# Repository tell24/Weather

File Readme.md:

Weather

This is a home project to measure the following parameters without any moving parts:-

	Inside Temperature
	Inside Humidity
	
	Outside Temperature
	Outside Humidity

	Air Pressure

	Rain Fall  Rate  mm/hr
	Total Rain Fall  mm

	Wind Speed mean
	Wind Speed Gust
	Wind Direction

The system will use a variety of micro processors including dSPIC, ESP8266 and Arduino Boards.
Data will be stored on a google sheet.
Display of data will by by GitHub Pages

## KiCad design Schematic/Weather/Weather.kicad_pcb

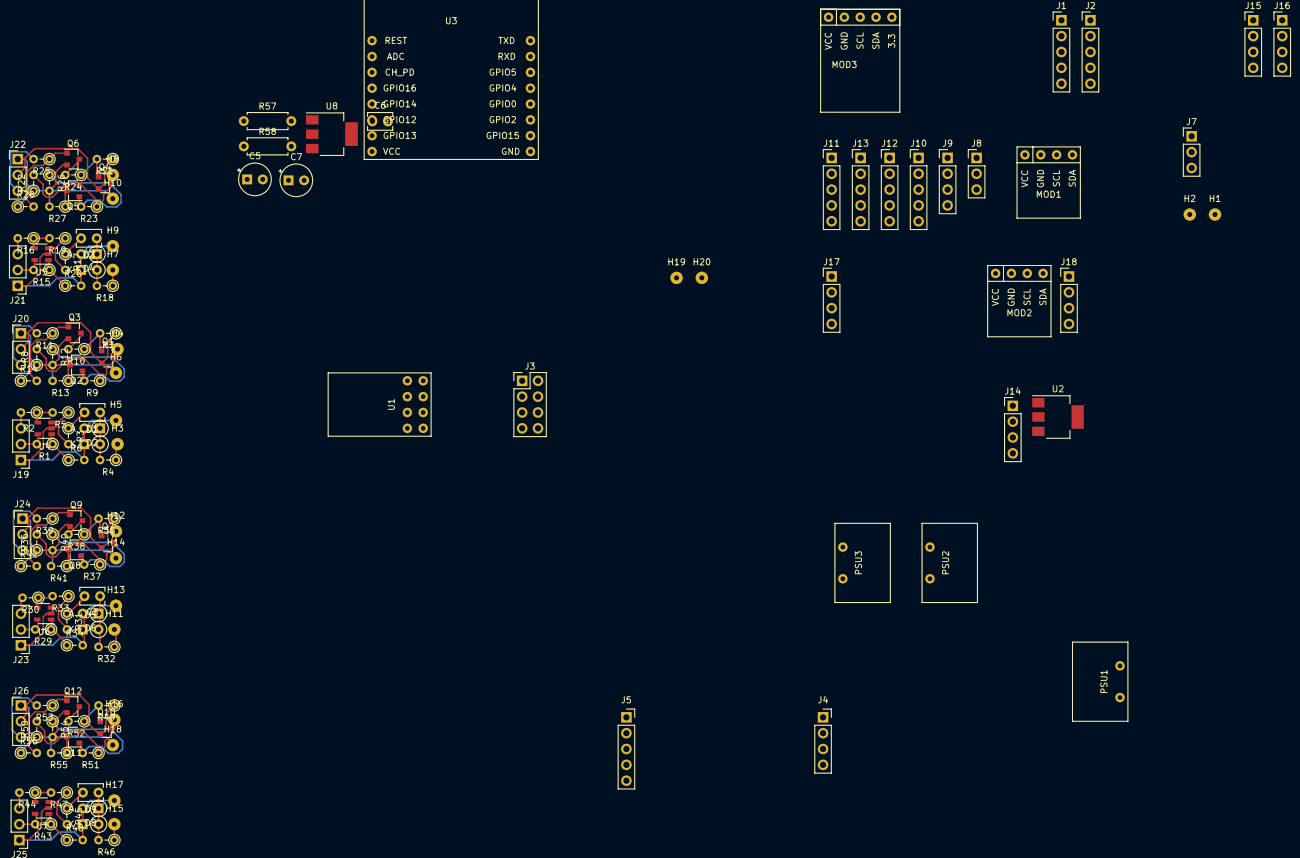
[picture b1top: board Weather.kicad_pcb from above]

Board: 2 copper layers, 144 parts (0 on the bottom side), 77 nets.

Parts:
C1, C2, C3, C4, C6: 0.1uF; C_Disc_D3.8mm_W2.6mm_P2.50mm
C5, C7: 47uF; CP_Radial_Tantal_D5.0mm_P2.50mm
D1, D3, D5, D7: in916; D_DO-35_SOD27_P2.54mm_Vertical_KathodeUp
D2, D4, D6, D8: in916; D_DO-35_SOD27_P2.54mm_Vertical_AnodeUp
H1, H2, H3, H4, H5, H6, H7, H8, H9, H10, H11, H12, H13, H14, H15, H16, H17, H18, H19, H20: MountingHole_Pad; SolderWirePad_1x01_Drill0.8mm
J1: Conn_01x05_Female; PinHeader_1x05_P2.54mm_Vertical
J2: Conn_01x04_Female; PinHeader_1x05_P2.54mm_Vertical
J3: Conn_02x04_Odd_Even; PinHeader_2x04_P2.54mm_Vertical
J4: 4_Way_Wire; PinSocket_1x04_P2.54mm_Vertical
J5: 5_Way_Wire; PinSocket_1x05_P2.54mm_Vertical
J7, J8, J19, J20, J21, J22, J23, J24, J25, J26: 3_Way_Wire; PinHeader_1x03_P2.54mm_Vertical
J9, J14, J15, J16, J17, J18: 4_Way_Wire; PinHeader_1x04_P2.54mm_Vertical
J10, J11, J12, J13: 5_Way_Wire; PinHeader_1x05_P2.54mm_Vertical
MOD1, MOD2: HTU21
MOD3: BMP180
PSU1, PSU2, PSU3: PowerBrick
Q1, Q2, Q4, Q5, Q7, Q8, Q10, Q11: AO3401; SOT-23
Q3, Q6, Q9, Q12: BSS138; SOT-23
R1, R2, R3, R5, R6, R15, R16, R17, R19, R20, R29, R30, R31, R33, R34, R43, R44, R45, R47, R48: 4.7K; R_Axial_DIN0204_L3.6mm_D1.6mm_P2.54mm_Vertical
R4, R18, R32, R46: 3.3k; R_Axial_DIN0204_L3.6mm_D1.6mm_P2.54mm_Vertical
R7, R21, R35, R49: 2.2k; R_Axial_DIN0204_L3.6mm_D1.6mm_P2.54mm_Vertical
R8, R22, R36, R50: 47K; R_Axial_DIN0204_L3.6mm_D1.6mm_P2.54mm_Vertical
R9, R12, R23, R26, R37, R40, R51, R54: 20K; R_Axial_DIN0204_L3.6mm_D1.6mm_P2.54mm_Vertical
R10, R24, R38, R52: 10K; R_Axial_DIN0204_L3.6mm_D1.6mm_P2.54mm_Vertical
R11, R25, R39, R53: 2.2K; R_Axial_DIN0204_L3.6mm_D1.6mm_P2.54mm_Vertical
R13, R27, R41, R55: 680; R_Axial_DIN0204_L3.6mm_D1.6mm_P2.54mm_Vertical
R14, R28, R42, R56: 5.1K; R_Axial_DIN0204_L3.6mm_D1.6mm_P2.54mm_Vertical
R57, R58: 4.7K; R_Axial_DIN0207_L6.3mm_D2.5mm_P7.62mm_Horizontal
U1: ESP-01v090; ESP-01
U2, U8: AMS1117; SOT-223-3_TabPin2
U3: ESP-12; ESP-12_breakout
U4, U5, U6, U7: LM321; SOT-23-5

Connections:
/Anenometer Control Board/J10_P1: D1.1, D2.2, H5.1, H6.1, J19.1, J20.1, Q3.2, R6.2, R8.1, R12.2, R13.2, R14.1, U4.2
/Anenometer Control Board/J10_P2: J19.2, R1.2, U4.5
/Anenometer Control Board/J10_P3: J19.3, R2.2
/Anenometer Control Board/J10_P4: J20.2, Q1.2, R7.1
/Anenometer Control Board/J10_P5: J20.3, R11.2
/Anenometer Control Board/J11_P2: J21.2, R15.2, U5.5
/Anenometer Control Board/J11_P3: J21.3, R16.2
/Anenometer Control Board/J11_P4: J22.2, Q4.2, R21.1
/Anenometer Control Board/J11_P5: J22.3, R25.2
/Anenometer Control Board/J12_P1: D5.1, D6.2, H13.1, H14.1, J23.1, J24.1, Q9.2, R34.2, R36.1, R40.2, R41.2, R42.1, U6.2
/Anenometer Control Board/J12_P2: J23.2, R29.2, U6.5
/Anenometer Control Board/J12_P3: J23.3, R30.2
/Anenometer Control Board/J12_P4: J24.3, R39.2
/Anenometer Control Board/J12_P5: J24.2, Q7.2, R35.1
/Anenometer Control Board/J13_P1: D7.1, D8.2, H17.1, H18.1, J25.1, J26.1, Q12.2, R48.2, R50.1, R54.2, R55.2, R56.1, U7.2
/Anenometer Control Board/J13_P2: J25.2, R43.2, U7.5
/Anenometer Control Board/J13_P3: J25.3, R44.2
/Anenometer Control Board/J13_P4: J26.2, Q10.2, R49.1
/Anenometer Control Board/J13_P5: J26.3, R53.2
/External ESP8266/J14_P1: J14.1, J15.1, J16.1, J17.1, J18.1, MOD2.1, U2.1
/External ESP8266/J14_P2: J14.2, J15.2, J16.2, J17.2, J18.2, MOD2.2, U3.6
/External ESP8266/J14_P3: J14.3, J15.3, J16.3, J17.3, J18.3, MOD2.3, U3.7
/External ESP8266/J14_P4: J14.4, J15.4, J16.4, J17.4, J18.4, MOD2.4, U2.3, U3.9
/Int Motherboard/J0_P2: C5.1, H1.1, H19.1, J1.4, J2.4, J4.4, J5.4, MOD1.4, MOD3.1, PSU1.2, U8.3
/Int Motherboard/J1_P2: J1.2, J2.2, J3.3, J4.2, J5.2, MOD1.2, MOD3.3, R58.2, U1.3
/Int Motherboard/J1_P3: J1.3, J2.3, J3.5, J4.3, J5.3, MOD1.3, MOD3.4, R57.2, U1.5
/Int Motherboard/J3_P6: C6.1, C7.1, J3.7, R57.1, R58.1, U1.7, U8.2
/PSU 2/J7_P1: J7.1, PSU2.2
/PSU 2/J7_P2: J7.2, PSU2.1, PSU3.1
/PSU 2/J7_P3: J7.3, PSU3.2
GND: C5.2, C6.2, C7.2, H2.1, H20.1, J1.1, J2.1, J3.2, J4.1, J5.1, MOD1.1, MOD3.2, PSU1.1, U1.2, U8.1
GNDS: D3.1, D4.2, H9.1, H10.1, J21.1, J22.1, Q6.2, R20.2, R22.1, R26.2, R27.2, R28.1, U5.2
unnamed: C1.1, D1.2, D2.1, R4.2
unnamed: C1.2, R3.1
unnamed: C2.1, D3.2, D4.1, R18.2
unnamed: C2.2, R17.1
unnamed: C3.1, D5.2, D6.1, R32.2
unnamed: C3.2, R31.1
unnamed: C4.1, D7.2, D8.1, R46.2
unnamed: C4.2, R45.1
unnamed: H3.1, H4.1, Q1.3, Q2.2, R4.1, R8.2, R9.1
unnamed: H7.1, H8.1, Q4.3, Q5.2, R18.1, R22.2, R23.1
unnamed: H11.1, H12.1, Q7.3, Q8.2, R32.1, R36.2, R37.1
unnamed: H15.1, H16.1, Q10.3, Q11.2, R46.1, R50.2, R51.1
unnamed: Q1.1, R7.2, R10.1
unnamed: Q2.1, R9.2, R12.1
unnamed: Q2.3, R13.1
unnamed: Q3.1, R11.1, R14.2
unnamed: Q3.3, R10.2
unnamed: Q4.1, R21.2, R24.1
unnamed: Q5.1, R23.2, R26.1
unnamed: Q5.3, R27.1
unnamed: Q6.1, R25.1, R28.2
unnamed: Q6.3, R24.2
unnamed: Q7.1, R35.2, R38.1
unnamed: Q8.1, R37.2, R40.1
unnamed: Q8.3, R41.1
unnamed: Q9.1, R39.1, R42.2
unnamed: Q9.3, R38.2
unnamed: Q10.1, R49.2, R52.1
unnamed: Q11.1, R51.2, R54.1
unnamed: Q11.3, R55.1
unnamed: Q12.1, R53.1, R56.2
unnamed: Q12.3, R52.2
unnamed: R1.1, R6.1, U4.1
unnamed: R2.1, R5.2, U4.4
unnamed: R3.2, R5.1, U4.3
unnamed: R15.1, R20.1, U5.1
unnamed: R16.1, R19.2, U5.4
unnamed: R17.2, R19.1, U5.3
unnamed: R29.1, R34.1, U6.1
unnamed: R30.1, R33.2, U6.4
unnamed: R31.2, R33.1, U6.3
unnamed: R43.1, R48.1, U7.1
unnamed: R44.1, R47.2, U7.4
unnamed: R45.2, R47.1, U7.3
unnamed: U2.2, U3.8

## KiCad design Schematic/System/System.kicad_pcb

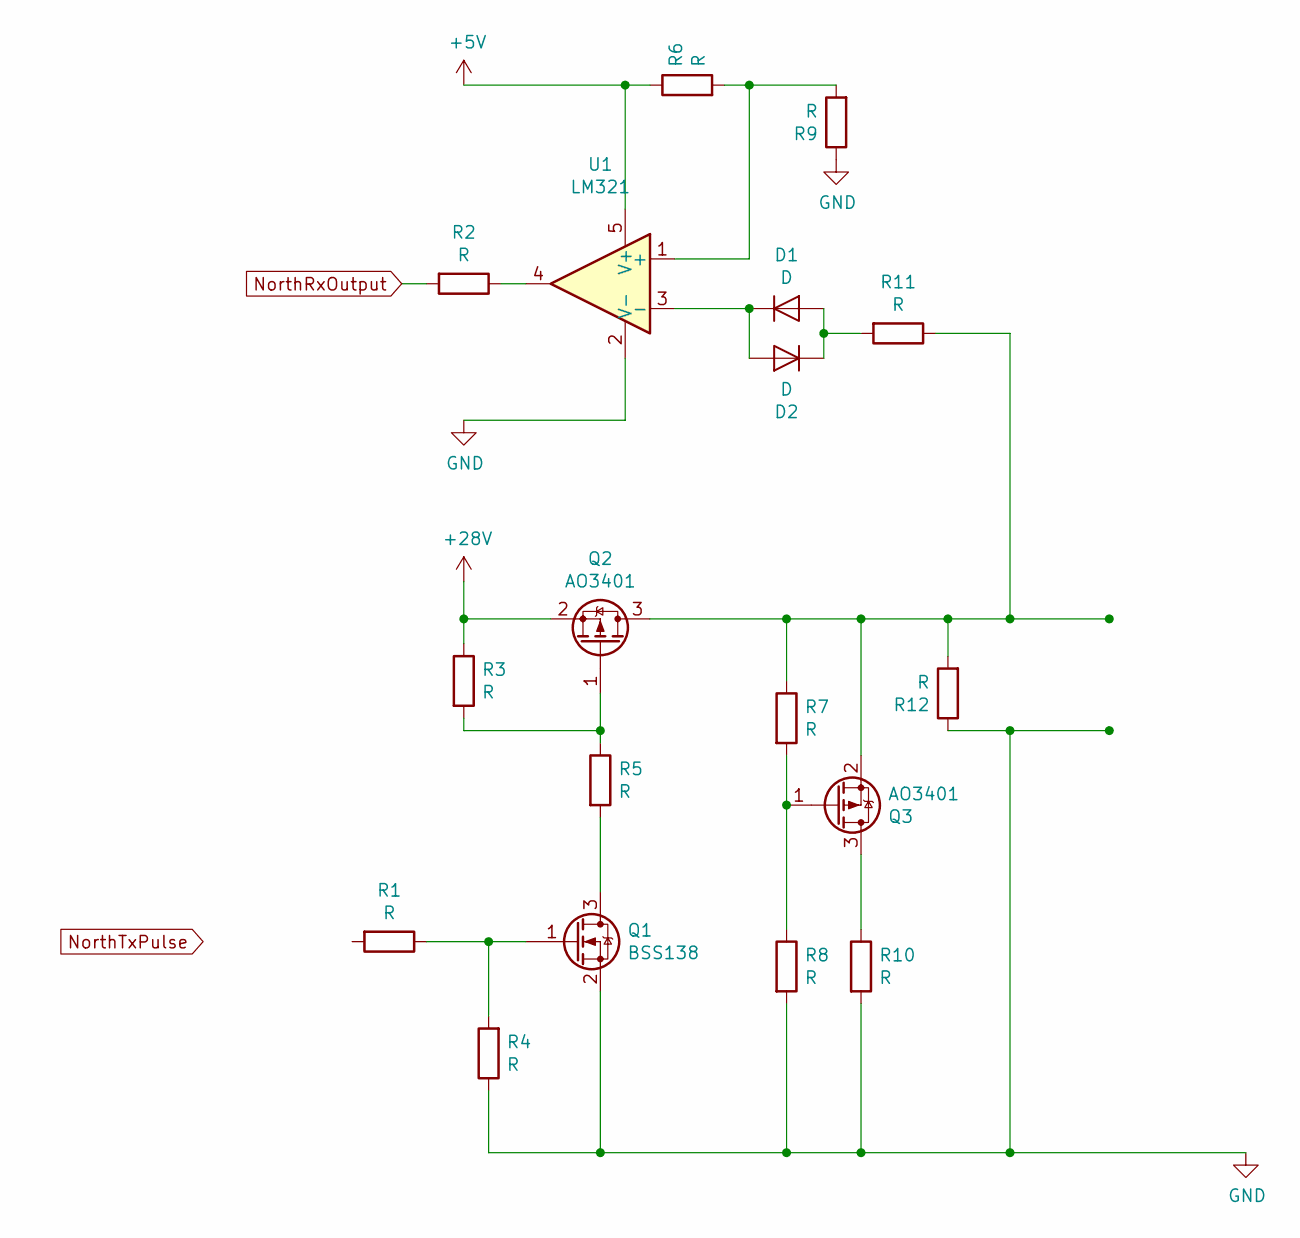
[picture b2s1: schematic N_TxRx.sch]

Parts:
D1, D2: D; D_DO-35_SOD27_P7.62mm_Horizontal
Q1: BSS138; SOT-23
Q2, Q3: AO3401; SOT-23
R1, R2, R3, R4, R5, R6, R7, R8, R9, R10, R11, R12: R; R_Axial_DIN0207_L6.3mm_D2.5mm_P7.62mm_Horizontal
U1: LM321; SOT-23-5

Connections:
+5V: R6.1, U1.5 (V+)
+28V: Q2.2 (S), R3.1
GND: Q1.2 (S), R4.1, R8.2, R9.1, R10.2, R12.1, U1.2 (V-)
unnamed: D1.1 (K), D2.2 (A), U1.3 (-)
unnamed: D1.2 (A), D2.1 (K), R11.2
unnamed: Q1.1 (G), R1.1, R4.2
unnamed: Q1.3 (D), R5.2
unnamed: Q2.1 (G), R3.2, R5.1
unnamed: Q2.3 (D), Q3.2 (S), R7.1, R11.1, R12.2
unnamed: Q3.1 (G), R7.2, R8.1
unnamed: Q3.3 (D), R10.1
unnamed: R2.1, U1.4
unnamed: R6.2, R9.2, U1.1 (+)
NorthRxOutput: R2.2

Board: 2 copper layers, 18 parts (0 on the bottom side), 13 nets, no tracks yet.

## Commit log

2019-02-12 Add readme text
2019-02-12 Elements added all sensors and webPage
2019-02-12 Publish webPage
2019-02-12 index moved
2019-02-13 esp8266 interrupt trigger
2019-02-14 correct high Hum to less than 100%
2019-02-14 Pointers added to gauges
2019-02-14 Temp Hum working
2019-02-15 wind
2019-02-15 pressure dial
2019-02-15 publish
2019-02-15 gust
2019-02-16 Peak
2019-02-16 Dial colour Black
2019-02-16 pre Dial Black
2019-02-16 Max Hum 100%
2019-02-16 Start rain
2019-02-17 rain
2019-02-17 pre ran
2019-02-17 Rain scale
2019-02-18 Clock
2019-02-18 is visible not working
2019-02-18 History start
2019-02-19 try about
2019-02-20 start jsChart
2019-02-20 Cart0
2019-02-20 sort graph ?
2019-02-21 canvas sort
2019-02-21 Current resize
2019-02-21 clock resize
2019-02-21 graph
2019-02-22 History change chart
2019-02-24 history
2019-02-24 canvas history
2019-02-25 graph v grid
2019-02-25 more graph draw
2019-02-25 history graph
2019-02-26 ReDraw
2019-02-27 charts less titles
2019-03-01 Publish1
2019-03-01 Cors Solved?
2019-03-02 Array
2019-03-02 history real temp
2019-03-03 chart progress
2019-03-03 chart better
2019-03-04 chart hour no titles
2019-03-04 chart hour ok
2019-03-05 Marker inserted
2019-03-05 day started
2019-03-06 move in progress
2019-03-06 move working
2019-03-07 Month progress
2019-03-08 Month plot okay
2019-03-08 Ledger inserted
2019-03-09 dropdown moves and curreny colours removed
2019-03-09 try tablet compatible 1
2019-03-09 title change
2019-03-10 Change layout now includes a sidebar
2019-03-10 docs folder update
2019-03-10 History size change
2019-03-10 Publish update
2019-03-10 rescale
2019-03-10 Resize to fit Tablet
2019-03-11 x-scale mod
2019-03-11 Add more data arrays
2019-03-12 moved back to google web designer
2019-03-12 min max changes
2019-03-13 chart colour sorted
2019-03-13 rain scale changed
2019-03-14 rain/wind no false data
2019-03-14 plot 0 rescale
2019-03-14 scale for Hum
2019-03-15 More scale correction
2019-03-17 schematics added
2019-03-17 more updates
2019-03-17 schematic changes
2019-03-18 Schematic project reset
2019-03-18 Start board layout
2019-03-20 Schematic restart
2019-03-22 More Board Data
2019-03-23 North TxRx diode change
2019-03-27 Start PCB
2019-03-27 small compnent changes
2019-03-28 Borad layout 2x for Tx Rx
2019-03-29 board rework
2019-03-30 update before south board added
2019-03-30 more board layouts
2019-04-08 toolchain changed
2019-04-08 More boards added
2019-04-09 Board update 4 channels
2019-04-10 new M_Board internal
2019-04-10 more changes
2019-04-10 Connector relable start
2019-04-11 Connector changes
2019-04-11 config connectors sda scl
2019-04-12 schm update
2019-04-24 Local webpage added
2019-04-25 local web page continues
2019-04-27 working local webpage
2019-04-27 I2C added
2019-05-01 RTCC EEPROM added
2019-05-02 eeprom added
2019-06-16 add Get Time
2019-06-16 more Date
2019-06-17 Date
2019-06-18 add stdarg
2019-06-18 laptop_changes
2019-07-16 USE STACK
2019-07-17 DST working
2019-07-28 Temp/Hum/Pressure read okay
2019-08-02 LCD Added
2019-08-03 Pre MPFS
2019-08-06 Start new data format
2019-08-09 remote update now working
2019-09-03 simple Client now works
2019-09-08 HTTP Forward added
2019-09-09 Add Test Software
2019-09-09 small Testing change
2019-09-09 script address change
2019-09-11 clock changed
2019-09-26 Testing software start adding data
2019-10-05 Outside bourd changed to work as server
2019-10-07 Combine Outside with HTTPForward
2019-10-08 Clock okay next step save data local
2019-10-12 Correct save data
2019-10-13 eeprom write delay (min 5ms between writes)
2019-10-21 Remote Data included in TCPClient.c
2019-10-27 Clock DST sorted
2019-12-03 Major change to remote board setup
2019-12-04 Index.html update new script
2019-12-04 New Script Name
2019-12-04 New script location
2019-12-04 Data Array Size Changed
2019-12-04 Add 1 to index
2019-12-05 start organise min max scale
2019-12-05 min_max 2
2019-12-05 min-max 3
2019-12-05 min-max 4
2019-12-05 Plot data sort correction
2019-12-05 More Graph updates
